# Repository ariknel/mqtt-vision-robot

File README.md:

# ESP32 MQTT Vision Robot

A line-following robot built around the **ESP32-DEVKITC V1**, featuring dual motor control via L298N, 3 IR line sensors, 3 ultrasonic distance sensors, and an LM2596S-ADJ buck converter powered by a custom 2S 18650 battery pack (8.4V fully charged). Fully controlled via a custom **Android MQTT app** with live telemetry, accelerometer tilt control, and WASD buttons.

All firmware is written in pure **ESP-IDF v5.x** (C). No Arduino framework. WiFi credentials are provisioned over BLE using NimBLE. Communication with the app uses MQTT over WiFi. The Android app runs an embedded MQTT broker — no cloud or external server needed.

---

## Table of Contents

- [Hardware Bill of Materials](#hardware-bill-of-materials)
- [Schematic](#schematic)
- [PCB Design Process](#pcb-design-process)
- [PCB Assembly & Testing](#pcb-assembly--testing)
- [Chassis — 3D Printed](#chassis--3d-printed)
- [Pinout Reference](#pinout-reference)
- [JST Connector Wiring](#jst-connector-wiring)
- [Power System](#power-system)
- [Motor Control](#motor-control)
- [Sensors](#sensors)
- [Firmware — Build & Flash](#firmware--build--flash)
- [Android App](#android-app)
- [First Run & WiFi Provisioning](#first-run--wifi-provisioning)
- [Control Modes](#control-modes)
- [Known Issues](#known-issues)
- [Build Log](#build-log)

---

## Hardware Bill of Materials

| Component | Part | Notes |
|-----------|------|-------|
| MCU | ESP32-DEVKITC V1 | Dual-core, WiFi + Bluetooth |
| Motor Driver | L298N | Desoldered from L298N breakout module — correct Schottky freewheeling diodes reused |
| Buck Converter | LM2596S-ADJ | 8.4V → 5V, output set via RV1 trimpot. Rectifier diode: SS34 Schottky |
| Battery | Custom 2S 18650 pack (2× 18650 cells) | 8.4V fully charged, connected via JST J3 (2-pin) |
| Charger | Hailege 2S USB-C BMS Boost Charger | Charges to 8.4V via USB-C (5V input), overcharge and overcurrent protection |
| IR Sensors | Generic IR reflectance module × 3 | Digital output, 3.3V logic — connected via JST-B (10-pin) |
| Ultrasonic Sensors | HC-SR04 × 3 — **2021+ version** | ECHO outputs 3.3V logic — no voltage divider needed. Connected via JST-A (10-pin) |
| OLED Display | SSD1306 128×32 I2C | Mounted on a separate daughter PCB above the main board |
| Android App | Custom (Kotlin, Android Studio, API 29+) | Embedded MQTT broker + WASD / accelerometer control |

> The L298N was desoldered from a breakout module to reuse its Schottky freewheeling diodes, which are the correct type and are already soldered in the correct polarity.

> The HC-SR04 **must** be the 2021+ version, whose ECHO pin outputs 3.3V logic. Earlier versions output 5V on ECHO and require a voltage divider before connecting to ESP32 GPIO. Check the PCB revision marking or measure with a multimeter before connecting.

---

## Schematic

### Full Schematic — Rev 2

*ESP32-DEVKITC V1 + LM2596S-ADJ power section + L298N motor driver + JST-A ultrasonic connector + JST-B IR / OLED connector*

### LM2596S-ADJ — Buck Converter & Battery Monitor

*8.4V input via J3 (2-pin JST). R1/R2 voltage divider (100 kΩ / 100 kΩ) feeds battery voltage to D34 for ADC monitoring. LM2596S-ADJ with SS34 Schottky diode D1, inductor L1, 220 µF input and output electrolytic capacitors, RV1 trimpot setting the 5V output via the FB pin.*

### L298N — Motor Driver

*L298N dual H-bridge with 8 Schottky freewheeling diodes. Motor A: IN1 (D13), IN2 (D14), EnA (D21). Motor B: IN3 (D27), IN4 (D26), EnB (D25). Motor outputs routed to J1 and J2 screw terminals.*

---

## PCB Design Process

The PCB is designed in **KiCad**. Custom component footprints are in the `/footprints` folder of this repo.

### Step 1 — Schematic Capture

Built in KiCad's schematic editor. The following components were not in KiCad's default library and were imported manually:

- ESP32-DEVKITC V1
- LM2596S-ADJ
- L298N
- JST-A and JST-B connectors

### Step 2 — Component Placement

Components were placed manually, following these principles:

- **LM2596 power section** — tight left-to-right cluster: input capacitor → IC → inductor → Schottky diode → output capacitor. Keeps the switching current loop short to minimise EMI.
- **L298N** — centered on the board, freewheeling diodes grouped tightly around each output pair.
- **ESP32-DEVKITC V1** — centered, GPIO pins facing the connector side to reduce trace crossings.
- **JST-A and JST-B** — right edge of the board for clean external cable routing.
- **J1/J2 screw terminals** — bottom edge for easy motor wire access.
- **J3 power connector** — left edge, close to the LM2596 input.

### Step 3 — Design Rules

Configured via **File → Board Setup → Design Rules → Net Classes**:

| Netclass | Track Width | Clearance | Applied To |
|----------|------------|-----------|------------|
| Default | 0.25 mm | 0.2 mm | All signal traces (GPIO, sensors, PWM) |
| Power | 1.0 mm | 0.8 mm | GND, 8.4V battery rail, 5V rail, motor output nets |

Power netclass assigned to: `GND`, `Net-(J3-Pin_2)` (8.4V battery), `Net-(JST-A1-Pin_1)` (5V rail), `Net-(J1-Pin_1/2)` (Motor A outputs), `Net-(J2-Pin_1/2)` (Motor B outputs).

### Step 4 — Board Outline

Rectangle drawn on the `Edge.Cuts` layer with ~5 mm clearance around all components using **Place → Rectangle**.

### Step 5 — Mounting Holes

4× `MountingHole_4.3x6.2mm_M4_Pad` placed at each corner for chassis standoff mounting. References set to H1–H4 (required for FreeRouter SES import compatibility).

### Step 6 — DRC (pre-routing)

Run via **Inspect → Design Rules Checker → Run DRC**:
- 3 silkscreen overlap warnings — fixed
- 0 footprint errors
- 69 unconnected pads (expected before routing)

### Step 7 — Auto-Routing with FreeRouter

1. **File → Export → Specctra DSN**
2. Open in FreeRouter, run the auto-router
3. **File → Import → Specctra Session (.ses)**
4. Review all traces manually and re-run DRC

Post-import DRC found 28 violations: decorative text placed on F.Cu (causing trace conflicts), IC pad spacing vs. power clearance rule violations, and 3 dangling track stubs. All fixed:
- Decorative text moved to F.Silkscreen layer
- Power clearance reduced from 0.8 mm to 0.5 mm to match IC footprint pad spacing
- 3 dangling stubs deleted

Final DRC: **0 errors, 2 warnings** (mounting hole library mismatch — ignorable).

*Fully routed 2-layer PCB. Red = F.Cu, blue = B.Cu. Thick traces = Power netclass (0.8 mm), thin = Default (0.25 mm).*

### Step 8 — Gerber Export & Manufacturing

> Board is production-ready. Final DRC: 0 errors.

1. **File → Plot** → Gerber format
2. Export all layers: F.Cu, B.Cu, F.Silkscreen, B.Silkscreen, F.Mask, B.Mask, Edge.Cuts + drill files
3. Submit to manufacturer — ordered as 2-layer, HASL finish, 5 copies

Gerber files are in the `/gerber` folder of this repo.

---

### OLED Display Board

A second small PCB was designed to mount a **SSD1306 128×32 I2C OLED** on top of the robot chassis. It sits above the main PCB, hides the main board from view, and connects back via the spare pins on JST-B.

The board contains no active components — just 4 solder test pads (H1–H4) for wire routing, a 4-pin JST connector (J5), and the OLED module footprint. Gerber files are in the `/gerber` folder alongside the main board gerbers.

**Why a separate board:**
- The main PCB had no remaining space for an OLED footprint
- Mounting on top of the chassis hides the main board for a cleaner look
- Can be detached and replaced independently from the main board

#### OLED Board Schematic

*J5 (4-pin JST) connects to H1 (GND), H2 (VCC), H3 (SCL), H4 (SDA). Short wires run from these pads to the OLED module pins.*

#### OLED Board PCB Layout

*Minimal PCB — 4 test pad holes + JST connector. Sits on top of chassis above the main board.*

#### OLED Board 3D View

#### OLED — JST-B Connection

The OLED board connects using the spare pins on JST-B (the IR sensor connector):

| JST-B Pin | Signal | OLED Board Pad | ESP32 GPIO |
|-----------|--------|---------------|-----------|
| 6 | — spare — | — | — |
| 7 | SDA | H4 | D4 (Pin 5) |
| 8 | SCL | H3 | D5 (Pin 8) |
| 9 | VCC (5V) | H2 | — |
| 10 | GND | H1 | — |

> Verify your SSD1306 module accepts 5V on VCC. Most breakout modules have an onboard 3.3V LDO and accept 5V. Bare OLED modules without a regulator require 3.3V only.

> The ESP32's default I2C pins (D21/D22) are both used by the motor driver. I2C is remapped to D4 (SDA) and D5 (SCL) inside the ESP-IDF I2C driver configuration in `oled.c`.

#### OLED — What It Displays

| Line | Content |
|------|---------|
| 1 | Battery voltage |
| 2 | MQTT connection status |
| 3 | Current mode (MANUAL / LINE FOLLOW) |
| 4 | Robot state (FOLLOWING / AVOIDING / RECOVERING) |

---

## PCB Assembly & Testing

**Do not solder all components at once.** Bring up the power circuit first and verify the output voltage before soldering the ESP32 or any sensors. This protects the ESP32 from overvoltage if the trimpot is set incorrectly from the factory.

### Step 1 — Inspect the Received PCBs

- Check for visible manufacturing defects: solder bridges, missing soldermask, lifted pads
- Hold the PCB up to light to check copper layer alignment
- Verify silkscreen labels match the schematic reference designators

### Step 2 — Solder the Buck Converter Circuit Only

Solder only the following components. Leave everything else unpopulated.

| Ref | Component |
|-----|-----------|
| J3 | 2-pin JST power input connector |
| U_LM2596 | LM2596S-ADJ IC |
| D1 | SS34 Schottky diode — stripe (band) = cathode |
| L1 | Inductor |
| C_in | 220 µF electrolytic input capacitor — stripe = GND (negative) |
| C_out | 220 µF electrolytic output capacitor — stripe = GND (negative) |
| RV1 | Trimpot |
| R1, R2 | 100 kΩ resistors (battery ADC voltage divider) |

Do **not** solder: ESP32, L298N, JST-A, JST-B, J1/J2 screw terminals, or any sensors yet.

### Step 3 — Set the Buck Converter Output to 5V

This is the most critical step. The LM2596S-ADJ output voltage is set by RV1. If left at the wrong position it may output the full battery voltage (up to 8.4V) to the 5V rail, which will destroy the ESP32.

1. Connect the 2S 18650 battery pack to J3 (Pin 1 = GND, Pin 2 = battery positive)
2. Set your multimeter to DC voltage
3. Place probes across the output capacitor C_out (or the 5V rail test points)
4. Slowly adjust RV1 until the meter reads **5.0V**
5. Confirm the reading is stable with no oscillation
6. Disconnect the battery

### Step 4 — Verify the Battery ADC Divider

> The firmware ADC saturates when the divider midpoint exceeds ~3.1V, which corresponds to a battery voltage of ~6.2V. This is a hardware limitation — the battery reading shows ~6.2V on a healthy 2S pack and only starts falling below 6.2V when the pack is nearly depleted. The app thresholds are set at 6.0V / 5.5V to account for this. This can be fixed in software with some calculations.

### Step 5 — Solder Remaining Components

Now that the 5V rail is confirmed correct and safe:

| Ref | Component |
|-----|-----------|
| U_L298N | L298N motor driver IC + all 8 Schottky freewheeling diodes |
| U_ESP32 | ESP32-DEVKITC V1 |
| JST-A | 10-pin connector (ultrasonic sensors) |
| JST-B | 10-pin connector (IR sensors + OLED) |
| J1, J2 | Screw terminals (motor A and motor B outputs) |

Solder the OLED daughter board separately — it is a standalone PCB.

### Step 6 — Power-On Verification

1. Connect the battery to J3
2. The ESP32 should boot — the onboard LED comes on
3. Connect the ESP32 to a PC via USB
4. Open a serial monitor at **115200 baud**
5. You should see BLE provisioning log output: `I (xxx) PROV: advertising as "IoT-Robot"`

If nothing appears on the serial monitor:
- Check battery polarity on J3
- Re-measure the 5V rail — must be 5V, not higher
- Verify ESP32 is seated correctly and all pins are soldered

### Step 7 — Connect and Test Sensors

Connect sensors one at a time and watch the serial output:

1. **IR sensors (JST-B)** — move a reflective object under each sensor; the digital output should toggle between 0 and 1
2. **Ultrasonic sensors (JST-A)** — wave your hand in front of each sensor; distances should appear in the telemetry log
3. **OLED board** — connect via JST-B spare pins 7–10; the display should show battery voltage and MQTT status after provisioning
4. **Motors (J1, J2)** — connect motors and verify direction in manual mode via the Android app

---

## Chassis — 3D Printed

The robot chassis is designed in **Autodesk Inventor** and 3D printed in PLA. The STEP file is in the root of this repo for reference and modification.

*Autodesk Inventor assembly — PCB on standoffs, motor mounts, battery compartment, and sensor positions.*

**Design details:**
- IR sensors mount on the underside, facing down toward the ground for line detection
- HC-SR04 sensors mount on the front face in left, center, and right positions
- Motor mounts are integrated into the chassis base
- PCB sits on M4 standoffs matching the 4 corner mounting holes on the PCB
- Battery compartment is accessible from the bottom of the chassis

**Print settings used:** PLA, 0.2 mm layer height, 20% infill for non-structural sections, 50% infill for motor mounts and standoff pillars.

---

## Pinout Reference

### Motor Driver — L298N

| L298N Signal | ESP32 Label | ESP32 Pin | Type |
|-------------|-------------|-----------|------|
| IN1 | D13 | Pin 28 | Digital Output — Motor A direction |
| IN2 | D14 | Pin 26 | Digital Output — Motor A direction |
| EnA | D21 | Pin 11 | PWM Output — Motor A speed |
| IN3 | D27 | Pin 25 | Digital Output — Motor B direction |
| IN4 | D26 | Pin 24 | Digital Output — Motor B direction |
| EnB | D25 | Pin 23 | PWM Output — Motor B speed |

### Battery Monitor

| Function | ESP32 Label | ESP32 Pin | Notes |
|----------|-------------|-----------|-------|
| Battery ADC | D34 | Pin 19 | R1/R2 divider from J3 Pin 2. Input-only GPIO, ADC1 — WiFi safe |

### IR Line Sensors — JST-B (10-pin)

| Sensor | ESP32 Label | ESP32 Pin | Notes |
|--------|-------------|-----------|-------|
| IR Left | D32 | Pin 21 | ADC1 — WiFi/MQTT safe |
| IR Center | D33 | Pin 22 | ADC1 — WiFi/MQTT safe |
| IR Right | D15 | Pin 3 | Mild strapping pin — IR signal defaults LOW at boot, no conflict |

### Ultrasonic Sensors HC-SR04 (2021+) — JST-A (10-pin)

| Sensor | TRIG Label | TRIG Pin | ECHO Label | ECHO Pin | Notes |
|--------|-----------|----------|-----------|----------|-------|
| Left | D22 | Pin 14 | D35 | Pin 20 | ECHO input-only GPIO, ADC1 |
| Center | D23 | Pin 15 | D19 | Pin 10 | |
| Right | D18 | Pin 9 | D2 | Pin 4 | GPIO2 = onboard LED — LED flashes with echoes (cosmetic, sensor reads correctly) |

> HC-SR04 2021+: ECHO outputs 3.3V logic — direct connection to ESP32, no voltage divider needed.

### JST Power Connector — J3 (2-pin)

| Pin | Signal |
|-----|--------|
| 1 | GND |
| 2 | Battery positive (8.4V fully charged) |

### Complete GPIO Map

| Label | ESP32 Pin | Function | Type |
|-------|-----------|----------|------|
| D2 | Pin 4 | ECHO Right (ultrasonic) | Input |
| D4 | Pin 5 | OLED SDA | I2C |
| D5 | Pin 8 | OLED SCL | I2C |
| D13 | Pin 28 | Motor A IN1 | Output |
| D14 | Pin 26 | Motor A IN2 | Output |
| D15 | Pin 3 | IR Right | Input |
| D18 | Pin 9 | TRIG Right (ultrasonic) | Output |
| D19 | Pin 10 | ECHO Center (ultrasonic) | Input |
| D21 | Pin 11 | EnA — Motor A speed | PWM Output |
| D22 | Pin 14 | TRIG Left (ultrasonic) | Output |
| D23 | Pin 15 | TRIG Center (ultrasonic) | Output |
| D25 | Pin 23 | EnB — Motor B speed | PWM Output |
| D26 | Pin 24 | Motor B IN4 | Output |
| D27 | Pin 25 | Motor B IN3 | Output |
| D32 | Pin 21 | IR Left | Input — ADC1 |
| D33 | Pin 22 | IR Center | Input — ADC1 |
| D34 | Pin 19 | Battery ADC | Input — ADC1, input-only GPIO |
| D35 | Pin 20 | ECHO Left (ultrasonic) | Input — ADC1, input-only GPIO |

---

## JST Connector Wiring

### JST-A — Ultrasonic Sensors (10-pin)

| Pin | Signal | ESP32 Label | ESP32 Pin |
|-----|--------|-------------|-----------|
| 1 | 5V (shared VCC) | — | — |
| 2 | GND (shared) | — | GND |
| 3 | TRIG Left | D22 | Pin 14 |
| 4 | ECHO Left | D35 | Pin 20 |
| 5 | TRIG Center | D23 | Pin 15 |
| 6 | ECHO Center | D19 | Pin 10 |
| 7 | TRIG Right | D18 | Pin 9 |
| 8 | ECHO Right | D2 | Pin 4 |
| 9–10 | — spare — | — | — |

### JST-B — IR Line Sensors + OLED (10-pin)

| Pin | Signal | ESP32 Label | ESP32 Pin |
|-----|--------|-------------|-----------|
| 1 | 3.3V (shared VCC) | — | — |
| 2 | GND (shared) | — | GND |
| 3 | IR Left | D32 | Pin 21 |
| 4 | IR Center | D33 | Pin 22 |
| 5 | IR Right | D15 | Pin 3 |
| 6 | — spare — | — | — |
| 7 | OLED SDA | D4 | Pin 5 |
| 8 | OLED SCL | D5 | Pin 8 |
| 9 | OLED VCC (5V) | — | — |
| 10 | OLED GND | — | GND |

VCC and GND are daisy-chained across all sensors within each connector group.

---

## Power System

```
[2S 18650 Battery Pack — 8.4V fully charged]
          │
       J3 (2-pin JST)  —  Pin 1: GND,  Pin 2: 8.4V
          │
          ├── R1 / R2 voltage divider (100 kΩ / 100 kΩ) ──── D34 Pin 19 (battery ADC)
          ├── 220 µF bulk input capacitor
          ├── L298N VS pin  (motors run from raw battery voltage)
          │
       LM2596S-ADJ  (D1: SS34 Schottky, RV1 trimpot → FB → 5V out)
       Output: 220 µF capacitor
          │
         5V rail ─────────── HC-SR04 VCC (JST-A Pin 1)
          │                  OLED VCC (JST-B Pin 9)
          │
       ESP32-DEV VIN ──── onboard LDO ──── 3.3V rail ──── IR sensor VCC (JST-B Pin 1)
```

The motors are powered directly from the battery voltage through the L298N VS pin — they operate at the full battery voltage, not the regulated 5V. The 5V rail powers only the ultrasonic sensors and OLED. The ESP32's onboard LDO produces the 3.3V rail for IR sensors and internal logic.

---

## Motor Control

The robot uses differential drive with the L298N dual H-bridge. Speed is controlled by PWM on the Enable pins (EnA/EnB). Direction is set by the IN1–IN4 logic inputs.

### H-Bridge Truth Table (per channel)

| IN_A | IN_B | Result |
|------|------|--------|
| HIGH | LOW | Forward |
| LOW | HIGH | Reverse |
| LOW | LOW | Coast (free spin) |
| HIGH | HIGH | Brake |

### Differential Steering

| Action | Motor A (Left) | Motor B (Right) |
|--------|---------------|----------------|
| Forward | Full speed | Full speed |
| Turn Left | Reduced speed | Full speed |
| Turn Right | Full speed | Reduced speed |
| Hard Left | Stop | Full speed |
| Hard Right | Full speed | Stop |
| Reverse | Full back | Full back |
| Spin Left | Full back | Full forward |
| Spin Right | Full forward | Full back |

> **Hardware note:** Motor A (left) has IN1 and IN2 wired backwards on the PCB. This is corrected in firmware inside the `drive()` function by inverting the polarity sent to PIN_IN1/PIN_IN2 for Motor A only. All higher-level motor commands (forward, reverse, turn, spin) are unaffected.

---

## Sensors

### IR Line Sensors (×3)

3 IR reflectance sensors mounted under the chassis for line detection. Digital output, 3.3V modules, connected via JST-B.

- All three GPIOs are on ADC1 — WiFi and MQTT remain active while reading
- No level shifting required (sensors output 3.3V logic)
- Firmware applies a 2-consecutive-read debounce before accepting a new state

**MQTT telemetry topic:** `robot/telemetry/ir`
```json
{"left": 0, "center": 1, "right": 0}
```

`1` = line detected (dark surface), `0` = no line (bright surface).

### Ultrasonic Sensors HC-SR04 2021+ (×3)

3 ultrasonic distance sensors for obstacle detection (left, center, right), connected via JST-A. Powered from the 5V rail.

ECHO connects directly to ESP32 GPIO — no voltage divider required (2021+ version outputs 3.3V logic).

Distance measurement uses an **interrupt-driven ISR** (`GPIO_INTR_ANYEDGE`). The rising edge records a timestamp in µs; the falling edge computes the distance as `pulse_us / 58`. This replaces the earlier polling approach, which missed short echo pulses at distances under ~170 cm.

**MQTT telemetry topic:** `robot/telemetry/ultrasonic`
```json
{"left": 24, "center": 8, "right": 31}
```

Values are in centimetres.

---

## Firmware — Build & Flash

The firmware is written in **C using ESP-IDF v5.4.1**. No Arduino framework, no PlatformIO.

### Project Structure

```
firmware/
├── CMakeLists.txt          — project root (IDF project)
├── sdkconfig.defaults      — NimBLE enabled, 8 KB main stack
└── main/
    ├── CMakeLists.txt      — lists all source files and dependencies
    ├── main.c              — app_main + 10 ms main loop
    ├── config.h            — all pin definitions and constants
    ├── provisioning.c/h    — BLE credential provisioning (NimBLE + NVS)
    ├── sensors.c/h         — IR, ultrasonic (ISR-driven), battery ADC
    ├── state_machine.c/h   — autonomy logic + motor control
    ├── mqtt.c/h            — WiFi STA + esp-mqtt client (event-driven)
    └── oled.c/h            — SSD1306 raw I2C driver + 5×7 font (no external lib)
```

### Firmware Architecture

```
app_main
  ├── provisioning_init()   — blocks on first boot (BLE); loads NVS on subsequent boots
  ├── sensors_init()        — configures GPIO, ISR handlers, ADC
  ├── state_machine_init()  — initialises LEDC channels and motor GPIOs
  ├── mqtt_init()           — blocks until WiFi + MQTT connected
  └── oled_init()           — I2C probe, skip gracefully if no OLED

Main loop (10 ms period)
  ├── sensors_read_ir()
  ├── sensors_read_ultrasonic()
  ├── sensors_read_battery()
  ├── state_machine_update()
  ├── every 100 ms → mqtt_publish_telemetry()
  └── every 500 ms → oled_update()
```

### Building on Windows (Docker + WSL2)

Build runs inside a Docker Dev Container. Flashing runs via WSL2 Ubuntu.

**One-time setup:**

1. Install [Docker Desktop](https://www.docker.com/products/docker-desktop)
2. Install WSL2 Ubuntu — PowerShell as Administrator:
   ```
   wsl --install -d Ubuntu
   ```
3. Install usbipd — PowerShell as Administrator:
   ```
   winget install usbipd
   ```
4. Inside Ubuntu terminal, install esptool:
   ```bash
   sudo apt update && sudo apt install pipx -y
   pipx install esptool
   pipx ensurepath
   source ~/.bashrc
   ```
5. Add yourself to the dialout group (then close and reopen the Ubuntu terminal):
   ```bash
   sudo usermod -aG dialout $USER
   ```

**Build (each session):**

1. Make sure Docker Desktop is running
2. Open the `mqttvision` folder in VS Code
3. `Ctrl+Shift+P` → **Dev Containers: Reopen in Container**
4. In the integrated terminal:
   ```bash
   cd /project/firmware
   idf.py build
   ```

**Flash (each session):**

1. Attach the ESP32 to WSL2 — PowerShell as Administrator:
   ```
   usbipd list
   usbipd bind --busid <BUSID>
   usbipd attach --wsl --busid <BUSID>
   ```
   The BUSID is listed next to "Silicon Labs CP210x" or "CH340". It may change if you use a different USB port.

2. Fix USB permissions if needed — Ubuntu terminal:
   ```bash
   sudo chmod 666 /dev/ttyUSB0
   ```

3. Flash — Ubuntu terminal:
   ```bash
   cd /mnt/c/Users/<you>/Desktop/mqttvision/firmware/build
   esptool.py --chip esp32 -p /dev/ttyUSB0 -b 460800 --before default_reset --after hard_reset write_flash @flash_args
   ```

4. Open the serial monitor:
   ```bash
   screen /dev/ttyUSB0 115200
   ```
   Exit with `Ctrl+A` then `K`.

**Erase flash** (when NVS needs clearing — e.g. stale WiFi credentials):
```bash
esptool.py --chip esp32 -p /dev/ttyUSB0 erase_flash
```
Then re-flash using Step 3 above.

### Building on Linux (Arch / Ubuntu native)

**One-time setup (Arch):**
```bash
sudo pacman -S git cmake ninja python python-pip python-pipx
sudo usermod -aG uucp $USER        # log out and back in after this
git clone --recursive https://github.com/espressif/esp-idf.git ~/esp/idf
cd ~/esp/idf && git checkout v5.4.1 && ./install.sh esp32
echo 'source ~/esp/idf/export.sh' >> ~/.bashrc && source ~/.bashrc
idf.py --version                   # should show ESP-IDF v5.4.1
```

**Build and flash:**
```bash
cd path/to/mqttvision/firmware
idf.py build
idf.py -p /dev/ttyUSB0 flash monitor
```

If permission is denied on `/dev/ttyUSB0`: `sudo chmod 666 /dev/ttyUSB0` (permanent: `sudo usermod -aG uucp $USER` then log out/in).

### Key Constants (config.h)

```c
/* Motor pins — L298N */
#define PIN_IN1   13    /* Motor A direction (wired backwards on PCB — corrected in drive()) */
#define PIN_IN2   14
#define PIN_ENA   21    /* Motor A speed (PWM) */
#define PIN_IN3   27    /* Motor B direction */
#define PIN_IN4   26
#define PIN_ENB   25    /* Motor B speed (PWM) */

/* IR sensors */
#define PIN_IR_LEFT    32
#define PIN_IR_CENTER  33
#define PIN_IR_RIGHT   15
#define IR_LINE_VALUE   0    /* GPIO level when sensor is on a dark line */
#define IR_DEBOUNCE_READS  2

/* Ultrasonic sensors */
#define PIN_TRIG_LEFT    22
#define PIN_ECHO_LEFT    35
#define PIN_TRIG_CENTER  23
#define PIN_ECHO_CENTER  19
#define PIN_TRIG_RIGHT   18
#define PIN_ECHO_RIGHT    2  /* GPIO2 = onboard LED — flashes with echoes (cosmetic only) */
#define ULTRA_TIMEOUT_US  25000  /* ~4 m max range, abort echo wait after this */

/* OLED I2C */
#define PIN_OLED_SDA   4
#define PIN_OLED_SCL   5
#define OLED_ADDRESS   0x3C

/* Battery ADC — GPIO34, ADC1_CH6 */
#define PIN_BATTERY      34
#define BATTERY_R1       100000.0f
#define BATTERY_R2       100000.0f

/* Speed — 8-bit PWM duty (0–255) */
#define SPEED_BASE        150   /* default speed, overridden by app slider */
#define SPEED_AVOID        90   /* cautious obstacle avoidance speed */
#define SPEED_CORRECTION   75   /* gentle correction turn speed */
#define SPEED_POST_CORR    80   /* forward speed when re-acquiring line */
#define SPEED_RAMP_STEP     2   /* PWM duty added per 10 ms tick while on-line */

/* Obstacle thresholds (cm) */
#define OBSTACLE_WARN_CM  20
#define OBSTACLE_STOP_CM  12

/* State machine timing */
#define RECOVERY_SWEEP_MS    2000
#define RECOVERY_SPIN_MS     5000
#define AVOID_MIN_MS          500
#define POST_AVOID_FWD_MS     600
#define RECOVERY_CREEP_MS     150

/* Loop intervals */
#define TELEMETRY_INTERVAL_MS  100
#define OLED_UPDATE_MS         500
#define MAIN_LOOP_MS            10

/* BLE provisioning window on every boot */
#define BLE_PROV_WINDOW_MS  30000
```

### Autonomous Mode — State Machine

The firmware runs a 3-state machine when in autonomous (line-follow) mode:

```
         ┌──────────────┐
    ┌───▶│  FOLLOWING   │◀────────────┐
    │    └──────┬───────┘             │
    │           │ obstacle < 20 cm    │ line found
    │           ▼                     │
    │    ┌──────────────┐             │
    │    │   AVOIDING   │             │
    │    └──────┬───────┘             │
    │           │ line lost (0,0,0)   │ line found
    │           ▼                     │
    │    ┌──────────────┐             │
    └────│  RECOVERING  │─────────────┘
         └──────────────┘
               │ no line after 5 s
               ▼
            STOP — await manual override via MQTT
```

**FOLLOWING** — normal line tracking using the IR truth table below. In the table, `1` = line detected (sensor on dark surface), `0` = not on line.

| IR Left | IR Center | IR Right | Action |
|---------|-----------|---------|--------|
| 0 | 1 | 0 | Forward — centered on line |
| 0 | 1 | 1 | Curve right gently |
| 1 | 1 | 0 | Curve left gently |
| 0 | 0 | 1 | Turn right hard |
| 1 | 0 | 0 | Turn left hard |
| 1 | 1 | 1 | All sensors on line — forward |
| 1 | 0 | 1 | Junction or crossing — continue forward |
| 0 | 0 | 0 | Line lost — enter RECOVERING |

**AVOIDING** — triggered when any ultrasonic sensor reads < 20 cm. Robot curves around the obstacle using the left/right distance comparison to choose which side to go, keeping the outer IR sensor tracking the line edge for as long as possible.

**RECOVERING** — all IR sensors show 0 (line lost):
1. Remember which side sensor was last active
2. Slow down, turn that direction for up to 2 s
3. If line is found → return to FOLLOWING
4. If not found after 2 s → slow 360° spin scan
5. If still not found → stop and wait for manual override via MQTT

In **manual mode**, the state machine is bypassed entirely. MQTT move commands drive the motors directly.

---

## Android App

The Android app is built in **Kotlin** with **Jetpack Compose** (no XML layouts), targeting **API 29 (Android 10+)**. It embeds a full MQTT broker — no external server or cloud service needed.

### Architecture

```
[Android Phone]
      │
      ├── Moquette MQTT Broker (foreground service, port 1883)
      │         │
      │         └── Eclipse Paho MQTT Client (subscribes + publishes)
      │
      │   Local WiFi Network
      │
[ESP32-DEVKITC V1]
      │
      └── esp-mqtt client (connects to phone IP:1883)
            ├── Subscribes: robot/control/move, mode, speed
            └── Publishes:  robot/telemetry/#
```

The phone's local WiFi IP address acts as the broker address. The ESP32 learns this IP during BLE provisioning and connects on port 1883.

**Connection sequence:**
1. App launches → Moquette broker starts as a foreground service on port 1883
2. `MainActivity` waits for `MqttBrokerService.isRunning`, then Paho connects to `localhost:1883`
3. ESP32 boots → 30-second BLE window expires → WiFi connects → esp-mqtt connects to phone IP:1883
4. Handshake complete — telemetry flows in, controls work

### File Structure

```
MqttVisionRobot/app/src/main/java/com/ariknel/mqttvisionrobot/
├── MainActivity.kt           — entry point, broker lifecycle, screen routing
├── MqttBrokerService.kt      — Moquette broker as Android foreground service
├── MqttClientManager.kt      — Eclipse Paho client, publish helpers
├── BleProvisioningManager.kt — BLE scan, connect, write credentials, receive reply
├── RobotState.kt             — global Compose state (telemetry, connection, mode)
├── TelemetryParser.kt        — parses robot/telemetry/# JSON into RobotState
├── RobotControlScreen.kt     — main control UI (StatusBar, D-pad, speed, tilt, telemetry)
└── ProvisioningScreen.kt     — BLE provisioning form (auto-detects broker IP)
```

### MQTT Topics

| Topic | Direction | Payload |
|-------|-----------|---------|
| `robot/control/move` | App → ESP32 | `forward` / `back` / `left` / `right` / `stop` |
| `robot/control/speed` | App → ESP32 | PWM value `0`–`255` |
| `robot/control/mode` | App → ESP32 | `manual` or `line_follow` |
| `robot/telemetry/ir` | ESP32 → App | `{"left":0,"center":1,"right":0}` |
| `robot/telemetry/ultrasonic` | ESP32 → App | `{"left":24,"center":8,"right":31}` |
| `robot/telemetry/battery` | ESP32 → App | `8.21` (float string, volts) |
| `robot/telemetry/speed` | ESP32 → App | `{"a":180,"b":180}` |

All messages use **QoS 0** (fire-and-forget). At a 100 ms telemetry rate, a missed packet is irrelevant.

### Telemetry Dashboard

| Widget | Source | Notes |
|--------|--------|-------|
| IR indicators | `robot/telemetry/ir` | 3 dot indicators — filled = line detected |
| Ultrasonic distances | `robot/telemetry/ultrasonic` | Live cm readouts Left / Center / Right |
| Battery voltage | `robot/telemetry/battery` | Colour-coded: green / amber / red |
| BROKER status | Internal | Live dot — Moquette running on phone |
| MQTT status | Internal | Live dot — ESP32 connected to broker |

### App UI

### Dependencies

```kotlin
// MQTT Broker — Moquette embedded
implementation("io.moquette:moquette-broker:0.17")

// MQTT Client — Eclipse Paho
implementation("org.eclipse.paho:org.eclipse.paho.client.mqttv3:1.2.5")
implementation("org.eclipse.paho:org.eclipse.paho.android.service:1.1.1")

// Coroutines — async broker startup
implementation("org.jetbrains.kotlinx:kotlinx-coroutines-android:1.7.3")
```

---

## First Run & WiFi Provisioning

WiFi credentials and the MQTT broker IP are not hardcoded in firmware. On first boot, the ESP32 advertises over BLE and waits for provisioning.

**BLE service details:**

```
Device name:    IoT-Robot
Service UUID:   4fafc201-1fb5-459e-8fcc-c5c9c331914b
Characteristic: beb5483e-36e1-4688-b7f5-ea07361b26a8  (WRITE + NOTIFY)

Write payload:  {"ssid":"YourWiFi","password":"YourPass","broker":"192.168.x.x"}
Reply (notify): "OK"  — credentials saved, ESP32 restarts into WiFi mode
                "ERR" — malformed JSON, try again
```

**Boot behaviour:**

| Condition | What happens |
|-----------|-------------|
| No credentials in NVS (first boot) | BLE advertises indefinitely until credentials are received |
| Credentials present, normal boot | BLE advertises for 30 s (re-provision window), then stops and connects to WiFi |
| Boot immediately after provisioning | BLE skipped entirely (`fresh` NVS flag set), goes straight to WiFi |

**Provisioning steps:**

1. Power on the robot — the ESP32 advertises as `IoT-Robot`
2. Open the Android app and tap **BLE PROVISIONING**
3. The app auto-detects the broker IP from the phone's WiFi interface — only the WiFi SSID and password need to be typed in manually
4. Tap **PROVISION** — the app writes the JSON credentials over BLE
5. The ESP32 replies with "OK" and restarts
6. After restarting, the ESP32 connects to WiFi then to the MQTT broker running on the phone
7. The app status bar shows **BROKER OK** and **MQTT** connected

**Re-provisioning:** Power on the robot and connect via BLE within 30 seconds of boot.

**Full reset:** Erase NVS to force a first-boot state:
```bash
esptool.py --chip esp32 -p /dev/ttyUSB0 erase_flash
```
Then reflash the firmware.

---

## Control Modes

The app has two independent mode axes that can be combined freely.

### Drive Source — WASD or Tilt

Toggled by the **TILT/WASD** button. The accelerometer listener is registered and unregistered on each toggle to preserve battery.

**WASD mode (default):**

```
      [ W ]
 [ A ][ S ][ D ]
      [STP]
```

Hold a button to move; releasing it sends `stop`. The speed slider sets the PWM value (0–255).

**Tilt mode (accelerometer):**

| Tilt direction | Action |
|---------------|--------|
| Forward | Move forward |
| Backward | Reverse |
| Left | Steer left |
| Right | Steer right |
| Flat | Stop |

Tilt speed is dynamic — a linear ramp from 80 to 255 as tilt angle increases. The speed slider updates in real time.

| Axis | Trigger threshold |
|------|------------------|
| Forward | `sensitivity − 0.6` (triggers slightly earlier for natural feel) |
| Left / Right | `sensitivity` |
| Reverse | `sensitivity + reverseGuard` |

A collapsible sensitivity panel (visible in tilt mode only) exposes two sliders:

| Slider | Effect |
|--------|--------|
| SENSITIVITY | Controls the trigger threshold for all axes |
| REVERSE GUARD | Extra tilt required to trigger reverse. Set to maximum (10) to disable reverse entirely |

### Autonomy — AUTO/MAN

Toggled by the **AUTO/MAN** button in the status bar.

- **MAN** — manual control via WASD or tilt. App publishes `manual` to `robot/control/mode`.
- **AUTO** — autonomous line-follow mode. App publishes `line_follow` to `robot/control/mode`. The control pad shows an "AUTO MODE" overlay and ignores all touch input. The ESP32 runs its state machine. The speed slider remains active — the firmware applies the current MQTT speed value in autonomous mode as well.

---

## Known Issues

| Priority | Issue | Status |
|----------|-------|--------|
| Critical | LM2596 trimpot-only FB risk — if the RV1 wiper fails open, the full battery voltage reaches the 5V rail and destroys the ESP32. Fix: add R_upper 1 kΩ (VOUT→FB) + R_lower 1 kΩ (FB→GND) with RV1 in series with R_lower as a failsafe floor | Next PCB revision |
| Warning | Low-ESR capacitor recommended on LM2596 220 µF output capacitor | To verify |
| Info | ECHO Right on GPIO2 — the onboard LED flashes in sync with right ultrasonic echoes. GPIO2 cannot be changed without a PCB revision. The sensor reads correctly; the flashing is cosmetic only. | Accepted |
| OK | L298N Schottky freewheeling diodes — repurposed from module, correct type and polarity | Done |
| OK | LM2596 D1 = SS34 Schottky | Done |
| OK | HC-SR04 2021+ — ECHO direct to ESP32 GPIO, no voltage divider | Done |
| OK | All IR GPIOs on ADC1 — WiFi and MQTT remain active during sensor reads | Done |
| OK | No strapping pin conflicts in final pinout | Done |
| OK | D34 battery ADC — ADC1, input-only GPIO, WiFi safe | Done |
| OK | J3: Pin 1 = GND, Pin 2 = battery positive (8.4V) | Done |
| OK | ESP32-DEVKITC V1 has onboard 100 nF decoupling — no external cap needed | Done |
| OK | GPIO36/GPIO39 do not exist on DEVKITC V1 — replaced with D19 and D2 | Done |
| OK | BLE invisible after first provisioning — fixed with 30 s re-provision window + `fresh` NVS flag | Done |
| OK | BLE and WiFi radio conflict — NimBLE kept alive and competed with WiFi — fixed with `stop_nimble()` clean handoff before WiFi init | Done |
| OK | OLED I2C blocking serial (720 ms/update) when no OLED connected — fixed with `i2c_master_probe()` presence check at init | Done |
| OK | Android broker IP returning cellular IP on dual-SIM phones — fixed by filtering `allNetworks` for WiFi transport only | Done |
| OK | Moquette failing silently (`catch Exception` missed Netty errors) — fixed with `catch Throwable` + `data_path = filesDir.absolutePath` | Done |
| OK | ESP32 ignoring the speed slider — added `robot/control/speed` subscription + `state_machine_set_speed()` | Done |
| OK | Motor A (left) IN1/IN2 wired backwards on PCB — corrected in `drive()` by inverting PIN_IN1/PIN_IN2 polarity for Motor A only | Done |
| OK | WASD fast-tap locks direction (`collectIsPressedAsState` missed short presses) — replaced with `pointerInput` + `awaitEachGesture` / `awaitFirstDown` / `waitForUpOrCancellation` | Done |
| OK | No AUTO/MAN mode toggle in app — AUTO/MAN button added to StatusBar; sends `line_follow` / `manual` to `robot/control/mode` | Done |
| OK | Autonomous speed ignored MQTT speed commands — all `m_*` motor helpers now scale from `s_speed` instead of hardcoded constants | Done |
| OK | Battery reading ~13V (wrong VREF, no calibration) — replaced with `adc_cali_line_fitting` + 8-sample averaging; fallback uses correct 3100 mV full-scale | Done |
| Warning | Battery divider 2×100 kΩ (1:1) saturates ADC above ~6.2V — a healthy 2S pack reads fixed at ~6.2V; only drops below when the pack is nearly dead. App thresholds set to 6.0V / 5.5V. | Hardware limitation — acceptable |
| OK | OLED I2C timeouts at 400 kHz — SCL reduced to 100 kHz, timeout extended to 50 ms; error counter: bus reset on 5th consecutive fail, auto-disable on 20th | Done |
| OK | Ultrasonic always reading 400 cm (polling loop missed short echo pulses < ~170 cm) — replaced with interrupt-driven ISR (`GPIO_INTR_ANYEDGE`) recording µs-precision timestamps | Done |

---

## Build Log

| Date | Entry |
|------|-------|
| 24 Apr 2026 | Rev 1 schematic complete. ESP32 + LM2596S-ADJ + L298N architecture established. |
| 24 Apr 2026 | EnA strapping conflict on D12 found and corrected → D21. |
| 24 Apr 2026 | R1/R2 confirmed as battery ADC voltage divider, not LM2596 feedback resistors. |
| 24 Apr 2026 | L298N repurposed from breakout module — correct Schottky freewheeling diodes confirmed. |
| 24 Apr 2026 | Android MQTT app architecture defined — embedded broker, dual control modes, telemetry dashboard. |
| 25 Apr 2026 | JST-A (ultrasonic) and JST-B (IR) connectors added to schematic and PCB. |
| 25 Apr 2026 | Full GPIO conflict check — all pins verified clean. |
| 25 Apr 2026 | HC-SR04 confirmed 2021+ version — voltage dividers removed from design. |
| 25 Apr 2026 | Final GPIO assignments locked in. LM2596 D1 = SS34 Schottky confirmed. |
| 25 Apr 2026 | Schematic Rev 2 exported — JST-A and JST-B fully connected. |
| 27 Apr 2026 | PCB design completed. L298N diode orientation corrected — all 8 diodes consistent anode/cathode orientation. |
| 27 Apr 2026 | Incorrect ESP32 footprint (WROOM-32D) found and replaced → ESP32-DEV DEVKITC V1. Custom footprints uploaded to `/footprints`. |
| 27 Apr 2026 | All pin numbers updated to DEVKITC V1 layout. GPIO36/39 replaced with D19/D2. 16 GPIOs used, 0 conflicts, 9 spare. |
| 27 Apr 2026 | DRC run — 3 silkscreen warnings fixed. 0 footprint errors. |
| 27 Apr 2026 | JST connector found placed upside down — fixed by flipping in KiCad PCB editor. |
| 27 Apr 2026 | Mounting hole references changed from numeric (1,2,3,4) to H1–H4 to resolve FreeRouter SES import error. |
| 27 Apr 2026 | FreeRouter auto-routing completed with 0 unrouted connections. Power netclass: 0.8 mm trace, 0.7 mm clearance. Signal: 0.25 mm trace, 0.2 mm clearance. |
| 27 Apr 2026 | SES imported into KiCad. All 28 DRC violations fixed: decorative text moved to F.Silkscreen, power clearance reduced to 0.5 mm to match IC pad spacing, 3 dangling stubs deleted. |
| 27 Apr 2026 | PCB routing complete. Final DRC: 0 errors, 2 warnings (mounting hole library mismatch — ignorable). Board is production-ready. |
| 27 Apr 2026 | GitHub URL added to PCB silkscreen. Gerber files exported and uploaded to `/gerber`. |
| 27 Apr 2026 | Power source confirmed: custom 2S 18650 pack (8.4V fully charged), charged via Hailege 2S USB-C BMS boost charger. |
| 27 Apr 2026 | Android app built and running. WASD + tilt mode, telemetry panel, speed slider. Dynamic tilt speed ramp, reverse guard, collapsible sensitivity panel added. |
| 27 Apr 2026 | Chassis design started in Autodesk Inventor. STEP file uploaded to repo. |
| 29 Apr 2026 | OLED board designed in KiCad — 128×32 SSD1306 I2C, separate PCB for mounting on chassis top. Connects via JST-B spare pins 7–10. ECHO Right moved D4 → D2; D4 and D5 assigned to OLED SDA/SCL. Gerbers added. |
| 29 Apr 2026 | Chassis assembly rendered in Autodesk Inventor. Assembly image added to repo. |
| 30 Apr 2026 | Final gerber review — main PCB and OLED board gerbers cross-checked. All layers verified (F.Cu, B.Cu, F.Silkscreen, B.Silkscreen, F.Mask, B.Mask, Edge.Cuts, drill). |
| 2 May 2026 | Main PCB and OLED board ordered from JLCPCB. 2-layer, HASL finish, 5 copies each. |
| 3 May 2026 | Firmware development started. All module headers defined: provisioning, sensors, state_machine, mqtt, oled. |
| 4 May 2026 | Chassis design finalised — mounting hole positions and motor mount spacing verified. |
| 4 May 2026 | sensors.c: IR reading with 2-read debounce, round-robin ultrasonic (non-blocking), battery ADC with voltage divider formula. state_machine.c skeleton. |
| 6 May 2026 | state_machine.c — 3-state machine (FOLLOWING / AVOIDING / RECOVERING) implemented. mqtt.c — WiFi connect, esp-mqtt event-driven client, telemetry JSON at 100 ms. |
| 7 May 2026 | provisioning.c — NimBLE GATT service, JSON credentials written to NVS. oled.c — SSD1306 raw driver, 5×7 font, battery + MQTT + mode/state display. |
| 8 May 2026 | main.c complete — all modules wired together and compiling. Chassis sent to 3D printer (PLA, 0.2 mm layer height, 20 % / 50 % infill). |
| 10 May 2026 | CLAUDE.md created. README audited and updated: OLED features, BLE provisioning section, constants. |
| 10 May 2026 | Auto-changelog hook configured in Claude Code — build log updated automatically after each code change. |
| 11 May 2026 | Full migration from Arduino to ESP-IDF v5.x. All .cpp files replaced with .c. Arduino framework, PubSubClient, ArduinoJson, and Adafruit SSD1306 removed. NimBLE replaces Bluedroid. esp-mqtt replaces PubSubClient. adc_oneshot API replaces legacy ADC. LEDC replaces ledcSetup/ledcWrite. I2C legacy driver with raw SSD1306 init sequence and 5×7 font inline. Motors merged into state_machine.c. Provisioning char upgraded to WRITE+NOTIFY. |
| 12 May 2026 | Android provisioning screen: broker IP auto-detected from phone's WiFi interface. WiFi network filter prevents cellular IP being selected on dual-SIM phones. Broker field is read-only with AUTO-DETECTED badge. |
| 12 May 2026 | HOW_TO_BUILD_AND_FLASH.txt updated: Ubuntu terminal open instructions, erase flash step corrected. |
| 13 May 2026 | BLE redesigned: 30 s re-provision window on every boot. `NVS_KEY_FRESH` flag skips BLE on boot immediately after provisioning. `stop_nimble()` (adv stop → port stop → 300 ms → deinit) called before WiFi init for clean radio handoff. |
| 13 May 2026 | OLED graceful no-hardware handling: `i2c_master_probe()` presence check at init. `s_present` guard in `oled_update()` eliminates 720 ms I2C blocking per loop when no OLED is connected. |
| 14 May 2026 | Android manifest: `FOREGROUND_SERVICE_CONNECTED_DEVICE` permission added — required for Android 14+ foreground service. |
| 14 May 2026 | Android `MainActivity`: fixed 1500 ms startup delay replaced with `MqttBrokerService.isRunning` poll — Paho connects only after Moquette has bound to port 1883. |
| 15 May 2026 | Moquette: `catch (Exception)` → `catch (Throwable)` so Netty startup errors surface in logcat. Root cause: H2 store path defaulting to `/data/` (permission denied). Fixed with `data_path = filesDir.absolutePath`. |
| 15 May 2026 | Android StatusBar: BROKER OK / BROKER DOWN indicator added as live Compose state. |
| 15 May 2026 | End-to-end MQTT verified: ESP32 connects to Moquette on phone, move / mode / speed commands received, telemetry published correctly. |
| 15 May 2026 | Speed control wired end-to-end: `TOPIC_SPEED` subscribed in `mqtt_init()`, `state_machine_set_speed()` added. `run_manual()` uses dynamic `s_speed` (turns use 2/3 of speed). |
| 19 May 2026 | PCBs arrived from JLCPCB. Buck converter circuit assembled (LM2596, diode, inductor, capacitors, trimpot, divider resistors). Output set to 5.0V and verified with multimeter. Battery ADC divider midpoint confirmed at ~4.2V. |
| 22 May 2026 | Remaining components soldered: ESP32, L298N, JST connectors, screw terminals. BLE provisioning functional — minor bugs noted: MQTT status indicator fires too early (shows connected before ESP32 reaches broker), GPIO watchdog trigger on sensor GPIOs. |
| 26 May 2026 | Motor driver tested — both channels functional. Mechanical on/off switch added to the battery line. |
| 28 May 2026 | Manual drive mode fully working. IR sensor data arriving in app correctly. Ultrasonic sensors under investigation (reading 400 cm). |
| 2 Jun 2026 | Motor A direction fixed — IN1/IN2 are wired backwards on the PCB hardware; corrected in `drive()` by inverting PIN_IN1/PIN_IN2 polarity for Motor A only. All move commands now correct. |
| 2 Jun 2026 | AUTO/MAN toggle added to app StatusBar. Sends `line_follow` / `manual` to `robot/control/mode`. D-pad shows overlay and ignores input when AUTO is active. |
| 2 Jun 2026 | WASD fast-tap fix — `collectIsPressedAsState` + `LaunchedEffect` replaced with `pointerInput` + `awaitEachGesture`. Fast taps now correctly send move on press and stop on release. |
| 2 Jun 2026 | Autonomous speed respects MQTT speed — all `m_*` motor helpers (forward, spin, curve, hard-turn) now scale from `s_speed`. Speed slider affects auto mode. |
| 2 Jun 2026 | Battery ADC calibration: `adc_cali_line_fitting` scheme added, 8-sample averaging, fallback uses 3100 mV full-scale (was 3300 mV). App thresholds updated to 6.0V / 5.5V to account for the 6.2V ADC saturation ceiling. |
| 2 Jun 2026 | OLED I2C stability: SCL reduced from 400 kHz to 100 kHz, timeout extended from 10 ms to 50 ms. Error counter: `i2c_master_bus_reset` on 5th consecutive fail, `s_present = false` on 20th (permanently stops updates if OLED disconnects). |
| 2 Jun 2026 | Ultrasonic sensors fixed: polling state machine replaced with interrupt-driven ISR (`GPIO_INTR_ANYEDGE`). Rising edge stores timestamp, falling edge computes `pulse_us / 58` cm. All three sensors now read correctly at all distances. |
| 2 Jun 2026 | ECHO Right confirmed on GPIO2 with ISR. GPIO36/39 were tried and rejected due to ESP32 WiFi/RTC errata causing spurious ISR triggers. Onboard LED flashing with echoes is cosmetic — accepted. |
| 4 Jun 2026 | First line-following calibration session. Test track: electrical tape on floor (~18 mm wide). Robot could detect the line but repeatedly drove off — speed too high for the IR reaction time, correction turns overshot. Speed and turn ratios adjusted iteratively during session. |
| 5 Jun 2026 | Second calibration session. Robot successfully followed a 90-degree curved section of tape at low speed. Motors occasionally failed to start from standstill — stall at low PWM duty; required a physical nudge to break static friction. Minimum startup speed noted as a tuning target. |
| 6 Jun 2026 | Third calibration session. Line following stable enough for consistent laps on the electrical tape track — robot stays on the line through gentle curves without intervention. Motor stall issue reduced by raising the minimum PWM floor. Behaviour considered stable enough for initial validation; further testing needed on a thicker line and sharper turns before calling calibration complete. |

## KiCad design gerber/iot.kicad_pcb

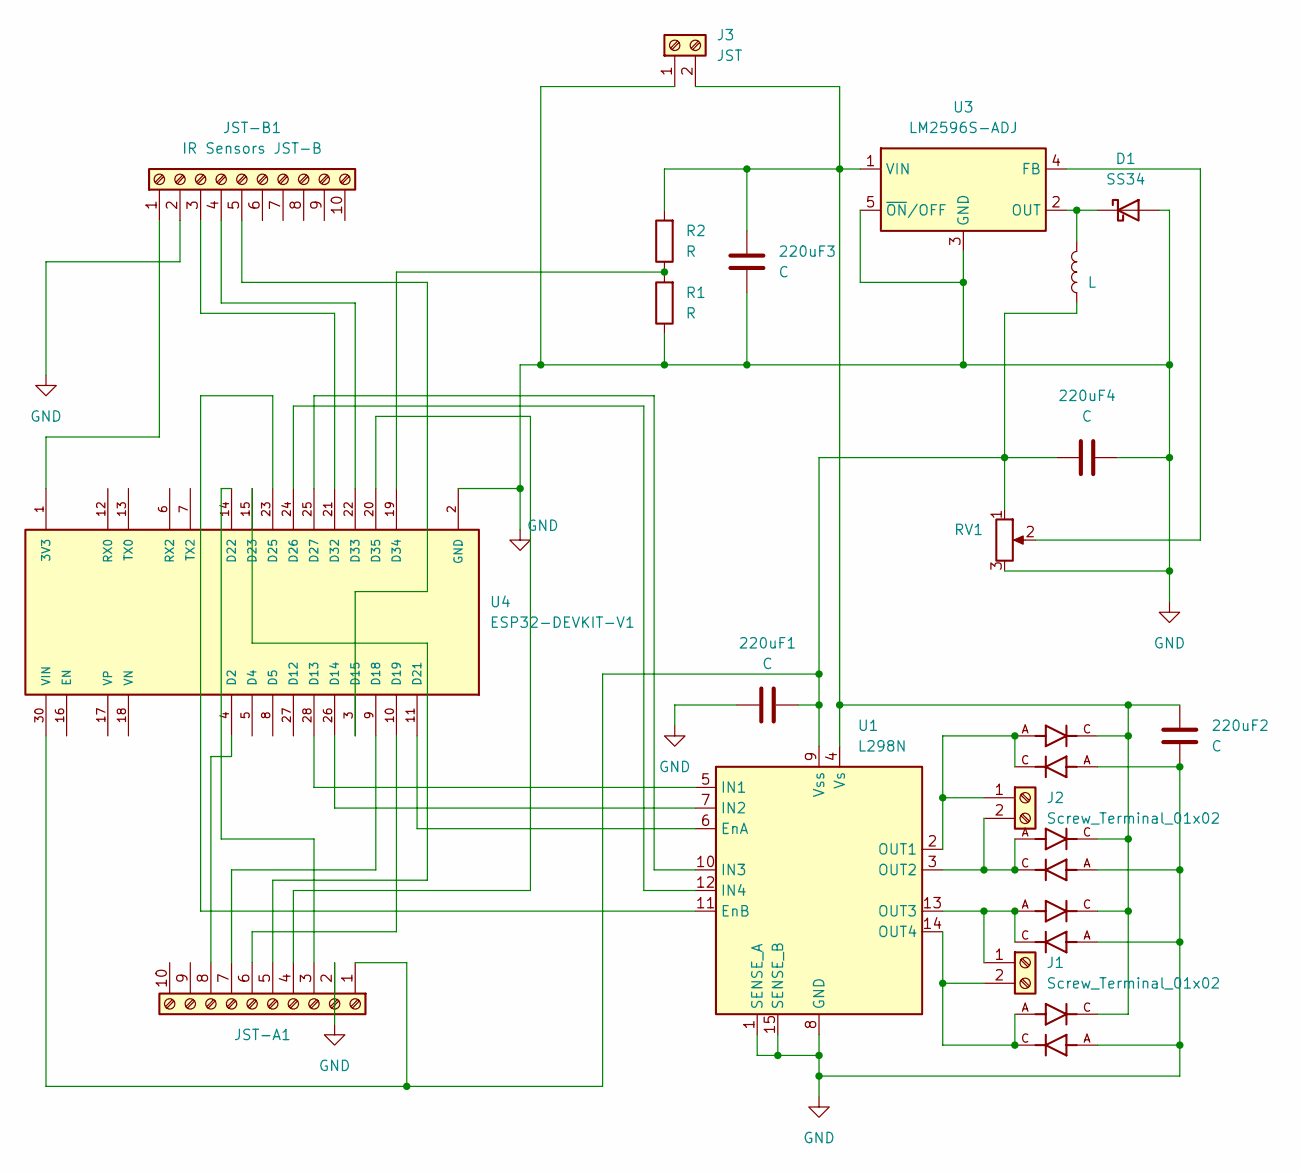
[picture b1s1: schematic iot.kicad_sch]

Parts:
220uF1, 220uF2, 220uF3, 220uF4: C; C_Elec_8x10.2
D1: SS34; D_SMA
D5, D6, D7, D8, D9, D10, D11, D12: M7; DIO_M7; PARTREV 2025-03-20
J1, J2: Screw_Terminal_01x02; TerminalBlock_MaiXu_MX126-5.0-02P_1x02_P5.00mm
J3: JST; JST_EH_B2B-EH-A_1x02_P2.50mm_Vertical
JST-A1: Ultrasonic SR-04 JST-A; JST_EH_B10B-EH-A_1x10_P2.50mm_Vertical
JST-B1: IR Sensors JST-B; JST_EH_B10B-EH-A_1x10_P2.50mm_Vertical
L1: L; L_Neosid_SM-NE127
R1, R2: R; R_Axial_DIN0207_L6.3mm_D2.5mm_P7.62mm_Horizontal
RV1: R_Potentiometer; Potentiometer_Bourns_3296W_Vertical
U1: L298N; TO-220-15_P2.54x5.08mm_StaggerOdd_Lead4.58mm_Vertical
U3: LM2596S-ADJ; TO-263-5_TabPin3
U4: ESP32-DEVKIT-V1; MODULE_ESP32_DEVKIT_V1; PARTREV N/A

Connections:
GND: 220uF1.1, 220uF2.2, 220uF3.1, 220uF4.2, D1.2 (A), D6.A, D8.A, D10.A, D12.A, J3.1, JST-A1.2, JST-B1.2, R1.1, RV1.3, U1.1 (SENSE_A), U1.8 (GND), U1.15 (SENSE_B), U3.3 (GND), U3.5 (~ON/OFF), U4.2 (GND), U4.29 (GND)
unnamed: D1.1 (K), L1.2, U3.2 (OUT)
unnamed: D9.A, D10.C, J1.1, U1.13 (OUT3)
unnamed: D11.A, D12.C, J1.2, U1.14 (OUT4)
unnamed: D5.A, D6.C, J2.1, U1.2 (OUT1)
unnamed: D7.A, D8.C, J2.2, U1.3 (OUT2)
unnamed: 220uF2.1, 220uF3.2, D5.C, D7.C, D9.C, D11.C, J3.2, R2.2, U1.4 (Vs), U3.1 (VIN)
unnamed: 220uF1.2, 220uF4.1, JST-A1.1, L1.1, RV1.1, U1.9 (Vss), U4.30 (VIN)
unnamed: JST-A1.3, U4.14 (D22)
unnamed: JST-A1.4, U4.20 (D35)
unnamed: JST-A1.5, U4.15 (D23)
unnamed: JST-A1.6, U4.10 (D19)
unnamed: JST-A1.7, U4.9 (D18)
unnamed: JST-A1.8, U4.4 (D2)
unnamed: JST-B1.1, U4.1 (3V3)
unnamed: JST-B1.3, U4.21 (D32)
unnamed: JST-B1.4, U4.22 (D33)
unnamed: JST-B1.5, U4.3 (D15)
unnamed: U1.6 (EnA), U4.11 (D21)
unnamed: U1.11 (EnB), U4.23 (D25)
unnamed: U1.5 (IN1), U4.28 (D13)
unnamed: U1.7 (IN2), U4.26 (D14)
unnamed: U1.10 (IN3), U4.25 (D27)
unnamed: U1.12 (IN4), U4.24 (D26)
unnamed: RV1.2, U3.4 (FB)
unnamed: R1.2, R2.1, U4.19 (D34)

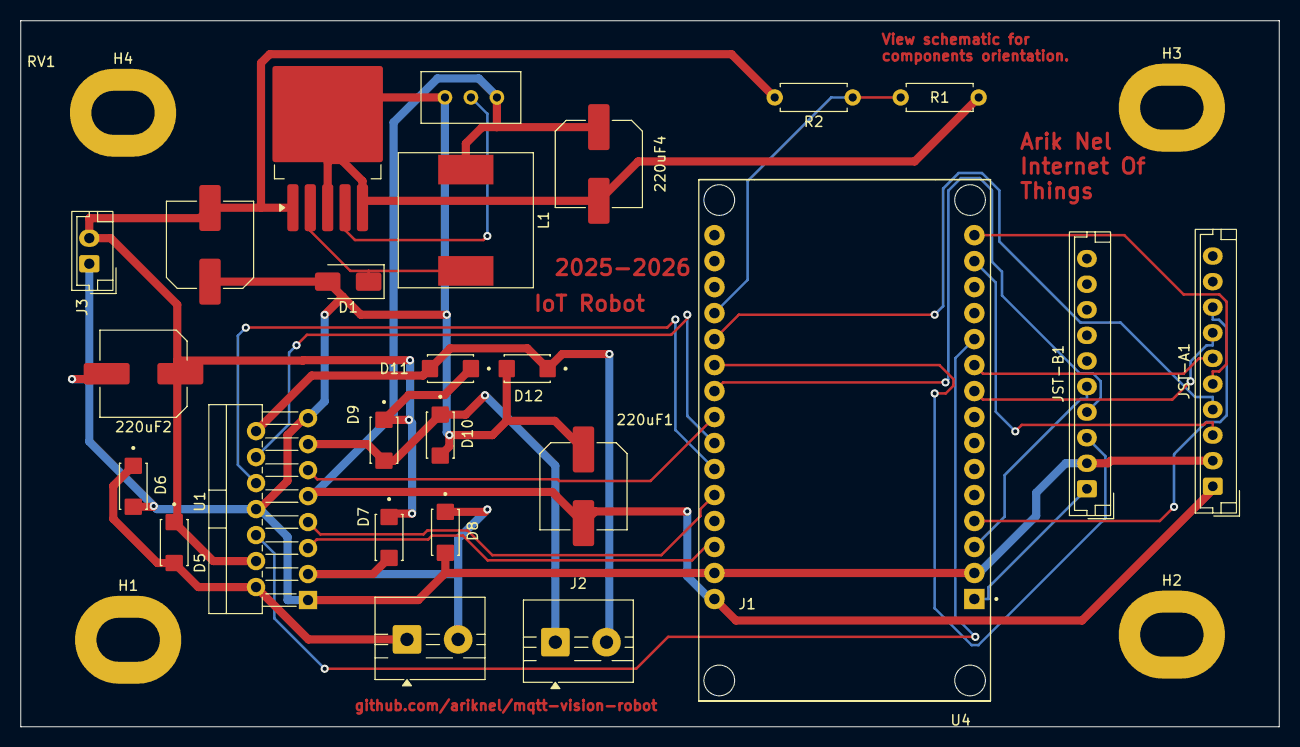
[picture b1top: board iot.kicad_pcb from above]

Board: 2 copper layers, 123.0 x 69.0 mm, 29 parts (0 on the bottom side), 26 nets.

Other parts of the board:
H1, H2, H3, H4: MountingHole_4.3x6.2mm_M4_Pad

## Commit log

2026-04-25 Added schematic files
2026-04-25 Rename schematic_full.png to schematic.png
2026-04-25 Update README with schematic update notice
    Added a note about schematic updates needed for the 5V input connection.
2026-04-27 Revise README with schematic updates and clarifications
    Updated schematic references and clarified LM2596 connection requirements.
2026-04-27 Fixed ESP32 Headers in pcb schematic
2026-04-27 Added image of pcb 3D
2026-04-27 Document PCB development process in README
    Added detailed PCB development process including schematic design, component placement, board outline, mounting holes, design rules check, auto-routing, and Gerber export steps.
2026-04-27 Change PCB layout image in README
    Updated PCB layout image in README from 'pcb_layout.png' to '3d.png'.
2026-04-27 Added kicad footprints
2026-04-27 Rename 3d.PNG to pcb_layout.png
2026-04-27 Rename pcb_routed.png to pcb_routed1.png
2026-04-27 Rename pcb_routed1.png to pcb_routed.png
2026-04-27 Clarify power source and charger details in README
    Updated power input and battery specifications for clarity.
2026-04-27 Added gerber files used for JLCPCB
2026-04-27 STEP FILE Voor in assembly inventor
    (robot chassis)
2026-04-27 Rename pcb_layout.PNG to pcb_layout.png
2026-04-27 Rename Screenshot_20260427-214831.png to app_front
2026-04-27 Rename app_front to app_front.png
2026-04-27 Upload app
    Kotlin
    api 29
2026-04-27 Added cad model for motor
    used inside inventor components assembly
2026-04-29 Rename oled_schematic.PNG to oled_schematic.png
2026-04-29 Updated schematic (VIAS FOR OLED)
2026-05-08 Defined structure
2026-05-15 Updated readme with all recent changes
2026-05-19 Revise README changelog for recent updates
    Updated changelog with recent project milestones, including migration from Arduino to ESP-IDF v5.x and PCB assembly status.
2026-05-22 Update README with recent project changes and testing
    Updated the build log with recent changes, including migration details and testing notes.
2026-05-25 Update README with motor driver test results
